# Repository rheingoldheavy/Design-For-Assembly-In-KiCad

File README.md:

Design-For-Assembly-In-KiCad
============================

How to design a board for assembly in KiCad

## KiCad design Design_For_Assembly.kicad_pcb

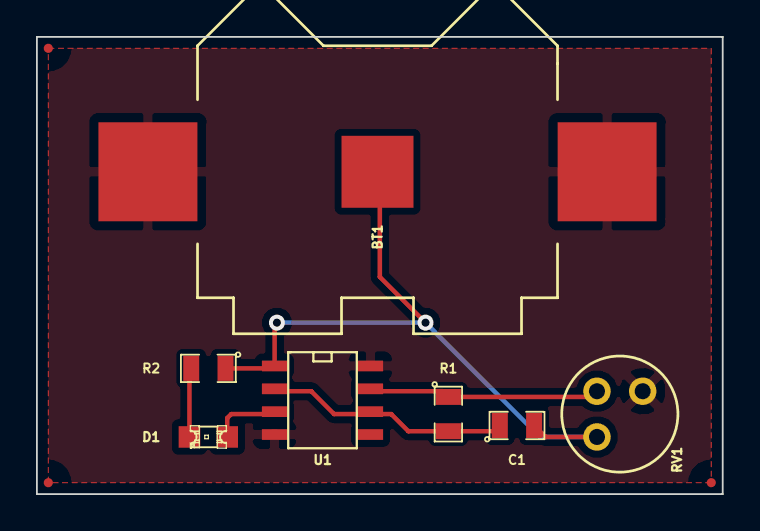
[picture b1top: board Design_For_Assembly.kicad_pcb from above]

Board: 2 copper layers, 38.1 x 25.4 mm, 10 parts (0 on the bottom side), 6 nets.

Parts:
BT1: CR2032; S8211_BATT_HOLDER
C1: 1uF; SM0805
D1: LED; LED-0805
FID1, FID2, FID3: FIDUCIAL; Fiducial
R1: 470K; SM0805
R2: 100; SM0805
RV1: 10K; POT_3339H
U1: 7555; SO8E_Oriented

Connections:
GND: BT1.2, C1.2, R2.1, RV1.3, U1.1
unnamed: D1.1, U1.3
unnamed: D1.2, R2.2
unnamed: C1.1, R1.2, U1.2, U1.6
unnamed: R1.1, RV1.2, U1.7
VCC: BT1.1, RV1.1, U1.4, U1.8

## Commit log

2014-09-16 Initial Commit
    All files generated during the creation of the Design For Assembly post
    at http://rheingoldheavy.com/design-assembly-kicad
2014-09-16 Design For Assembly In KiCad Project Files...
    This repo contains all the KiCad project files, CSV files and gerbers generating during the creation of the "Design for Assembly" post at http://rheingoldheavy.com/design-assembly-kicad. It is design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
